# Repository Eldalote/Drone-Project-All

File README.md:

# Drone-Project-All
Project repository for all the components of the Drone project

Project currently on hold. Unfortunately, with the current chip shortage, it would be very difficult to get the PCBs made and populated.
Several important chips are out of stock at all reputable distributors, and I fear that if I try to redesign with parts that I can get, that once I'm done redesigning, some other parts are out of stock.
For now, this project is on hold. I plan to return to it once the chip shortages have been at least somewhat resolved.

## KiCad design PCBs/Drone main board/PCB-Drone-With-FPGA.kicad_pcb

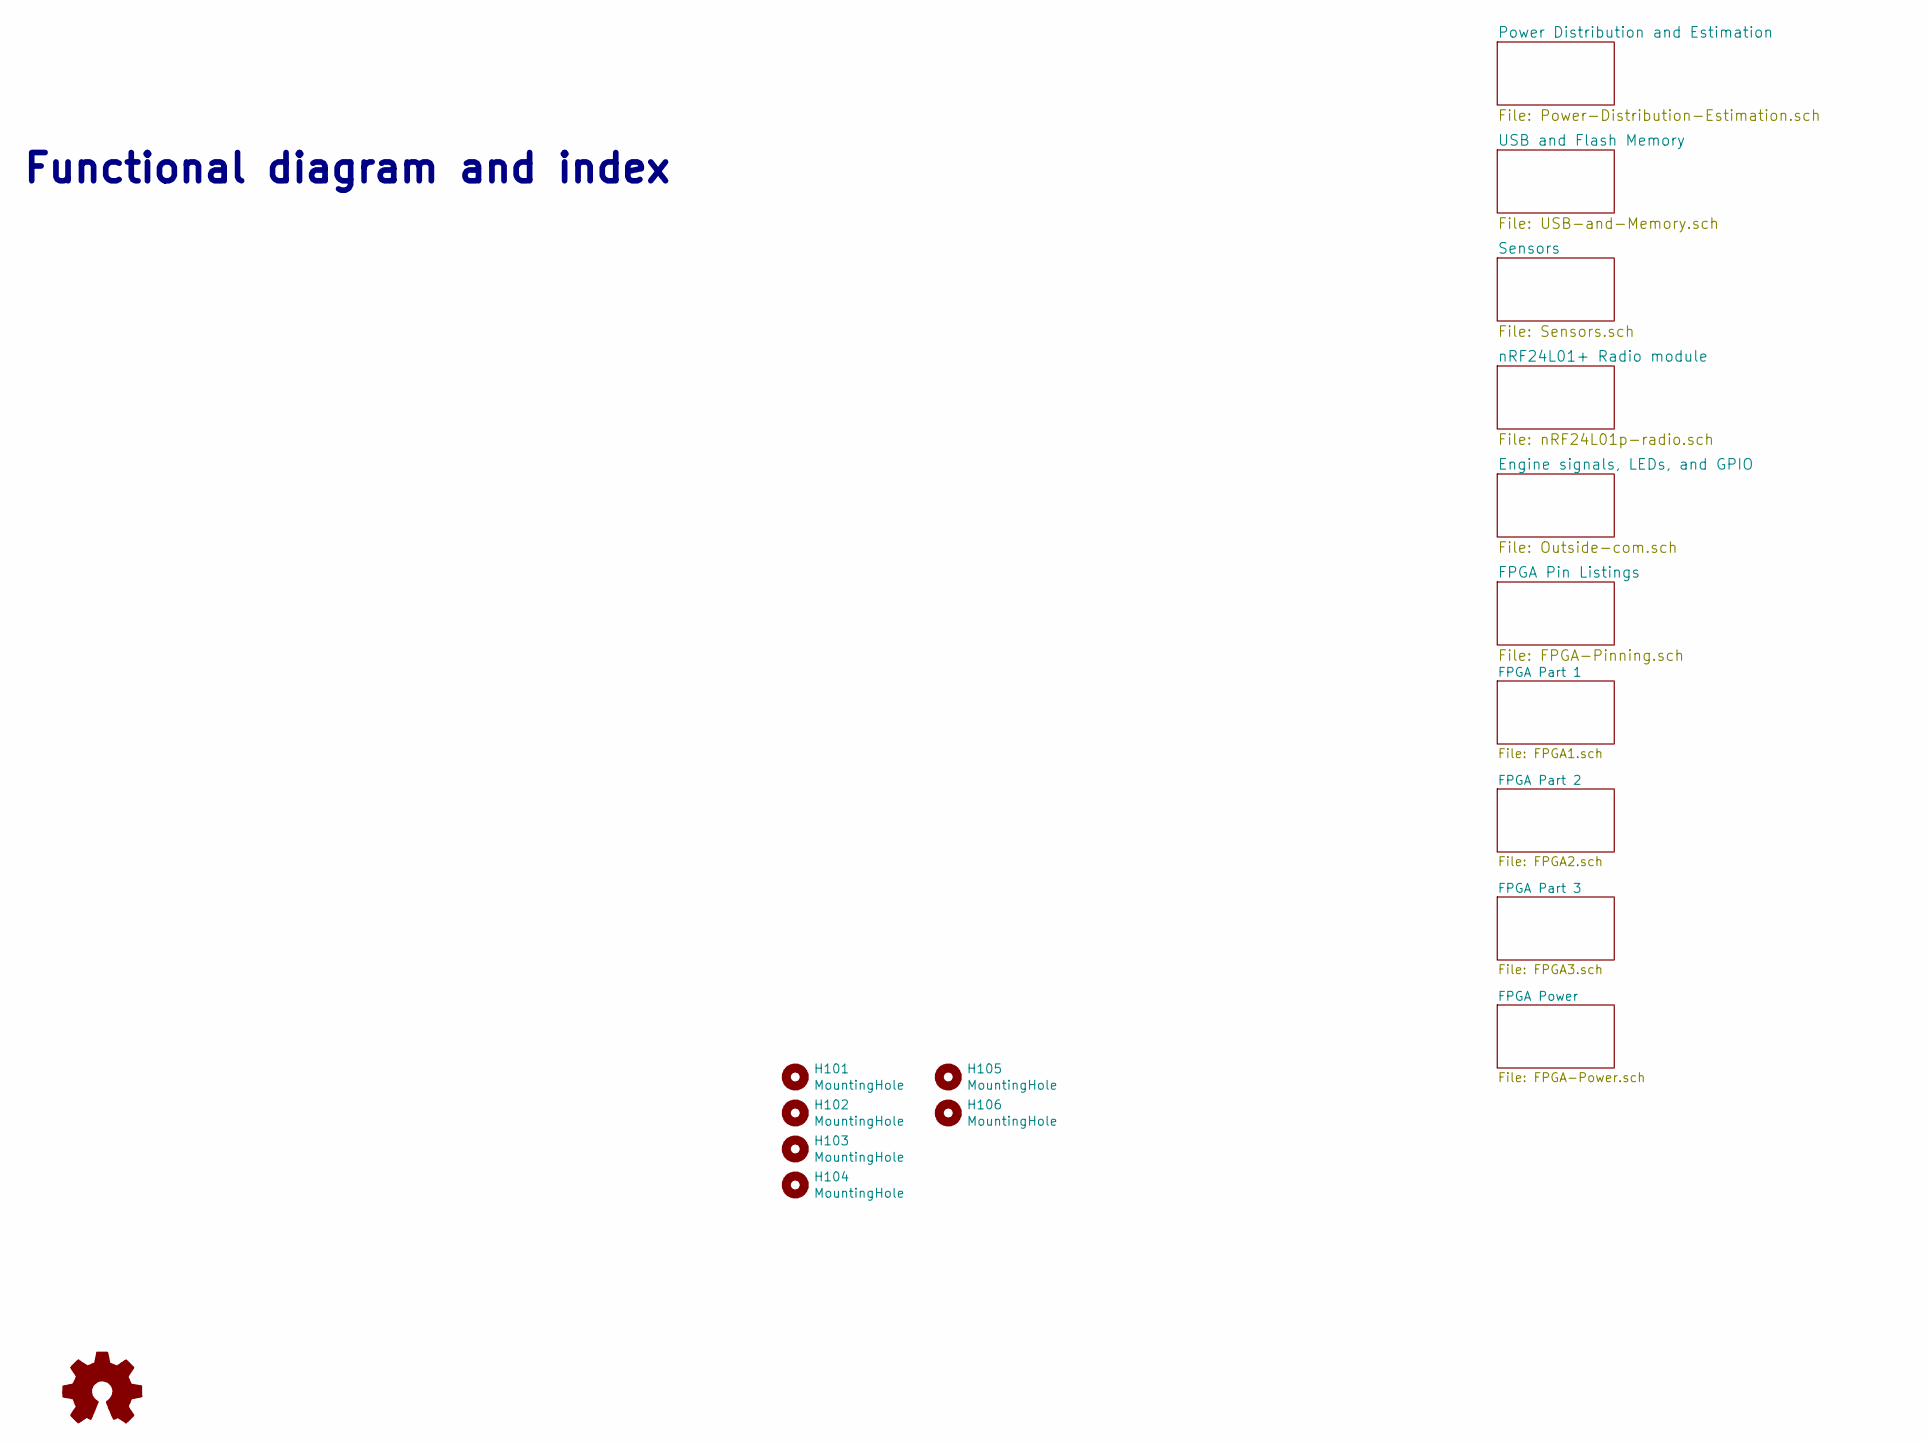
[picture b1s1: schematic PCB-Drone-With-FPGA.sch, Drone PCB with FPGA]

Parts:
H101, H102, H103, H104: MountingHole; MountingHole_3.2mm_M3
H105, H106: MountingHole; MountingHole_6mm
LOGO101: Logo_Open_Hardware_Small; OSHW-Logo_5.7x6mm_SilkScreen

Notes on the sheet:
Functional diagram and index

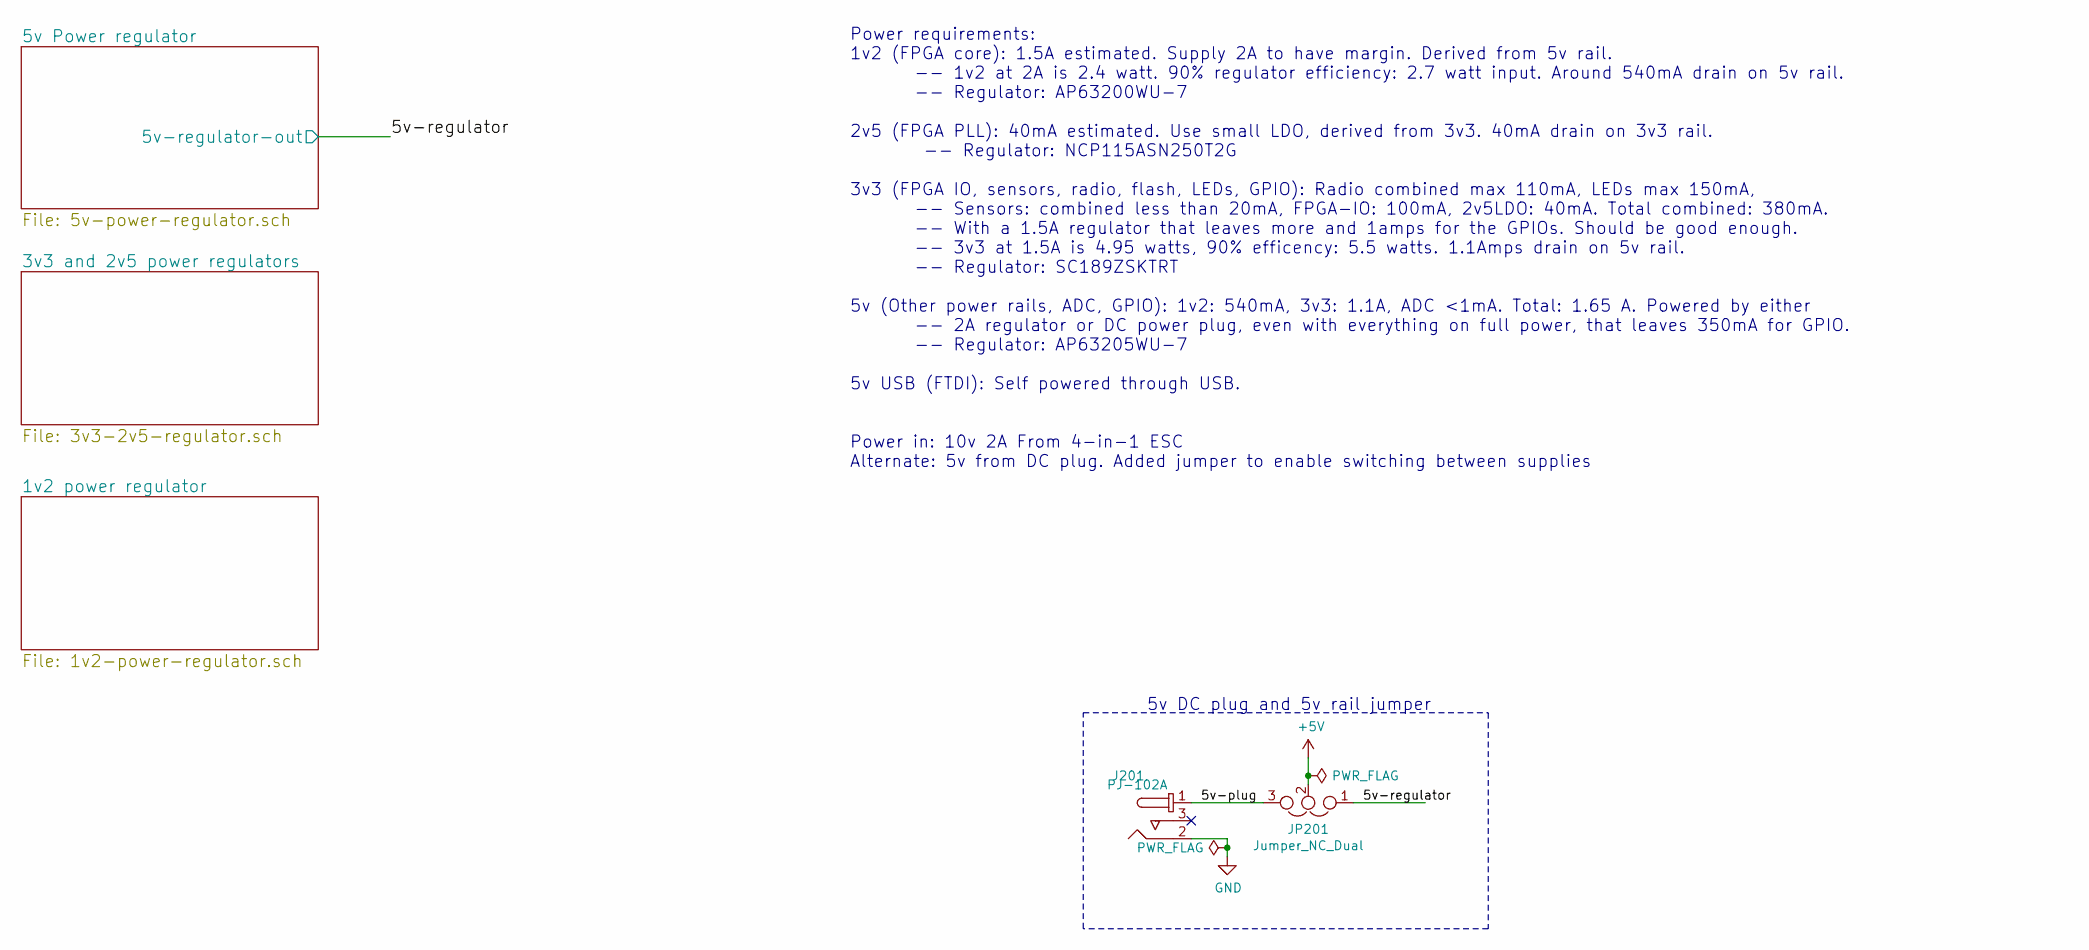
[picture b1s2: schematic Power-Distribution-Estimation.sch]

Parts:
J201: PJ-102A; Barrel_Jack_5.5mmODx2.1mmID_PJ-102A
JP201: Jumper_NC_Dual; PinHeader_1x03_P2.54mm_Vertical

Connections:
+5V: JP201.2; also elsewhere on the board
/Power Distribution and Estimation/5v-plug: J201.1, JP201.3
/Power Distribution and Estimation/5v-regulator: JP201.1; also elsewhere on the board
GND: J201.2; also elsewhere on the board

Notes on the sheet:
Power requirements: 1v2 (FPGA core): 1.5A estimated. Supply 2A to have margin. Derived from 5v rail. -- 1v2 at 2A is 2.4 watt. 90% regulator efficiency: 2.7 watt input. Around 540mA drain on 5v rail. -- Regulator: AP63200WU-7 2v5 (FPGA PLL): 40mA estimated. Use small LDO, derived from 3v3. 40mA dra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
5v DC plug and 5v rail jumper

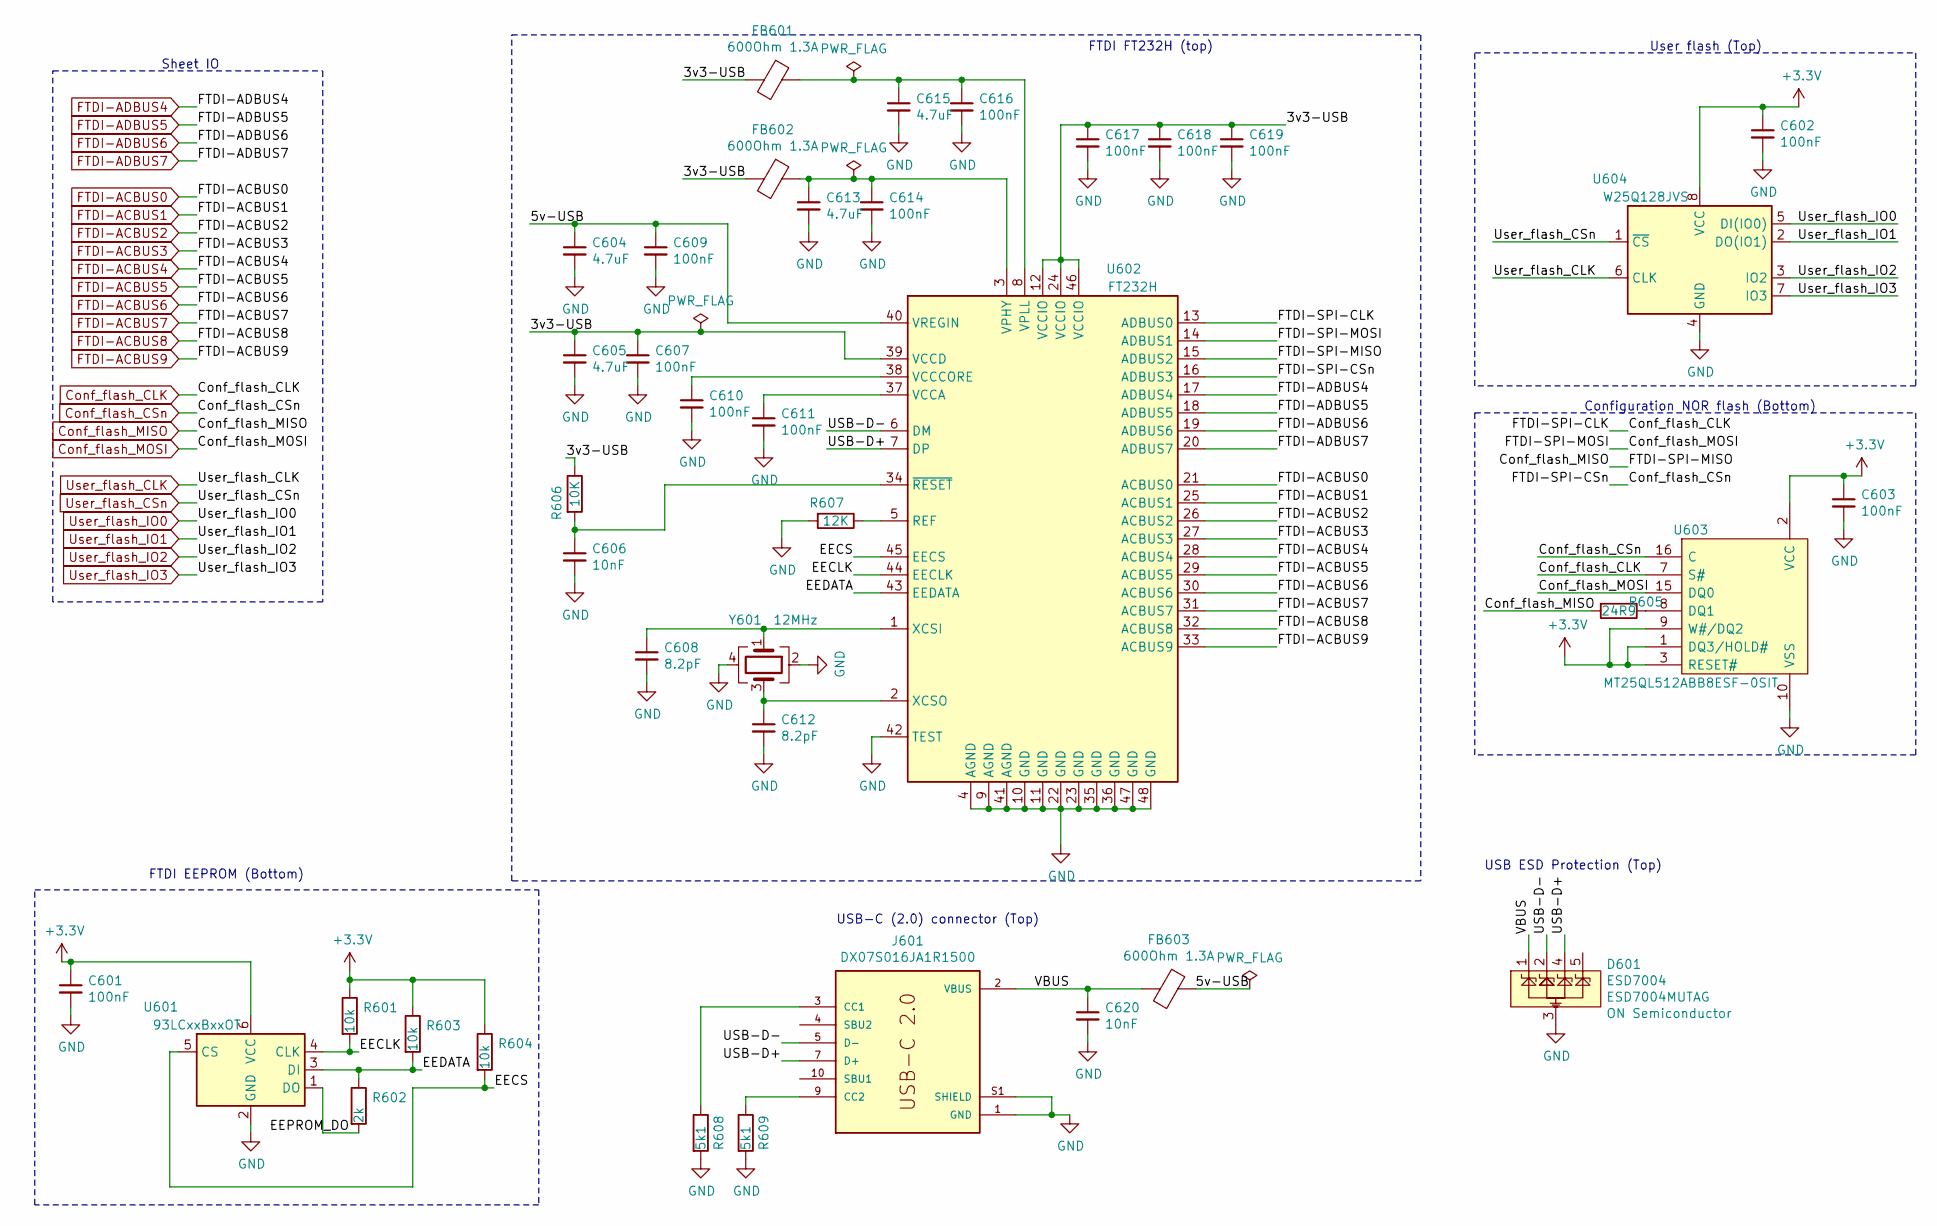
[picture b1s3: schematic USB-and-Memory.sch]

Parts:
C601, C602, C603, C607, C609, C610, C611, C614, C616, C617, C618, C619: 100nF; C_0402_1005Metric
C604, C605, C613, C615: 4.7uF; C_0402_1005Metric
C606, C620: 10nF; C_0402_1005Metric
C608, C612: 8.2pF; C_0402_1005Metric
D601: ESD7004; Diodes_UDFN-10_1.0x2.5mm_P0.5mm
FB601, FB602, FB603: 600Ohm 1.3A; R_0603_1608Metric
J601: DX07S016JA1R1500; JAE_DX07S016JA1R1500
R601, R603, R604: 10k; R_0402_1005Metric
R602: 2k; R_0402_1005Metric
R605: 24R9; R_0402_1005Metric
R606: 10K; R_0402_1005Metric
R607: 12K; R_0402_1005Metric
R608, R609: 5k1; R_0402_1005Metric
U601: 93LCxxBxxOT; SOT-23-6
U602: FT232H; LQFP-48_7x7mm_P0.5mm
U603: MT25QL512ABB8ESF-0SIT; SOIC127P1032X265-16N
U604: W25Q128JVS; SOIC-8_5.23x5.23mm_P1.27mm
Y601: 12MHz; Crystal NDK 3.2x2.5

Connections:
+3V3: C601.1, C602.1, C603.1, R601.1, R603.1, R604.1, U601.6 (VCC), U603.1 (DQ3/HOLD#), U603.2 (VCC), U603.3 (RESET#), U603.9 (W#/DQ2), U604.8 (VCC); also elsewhere on the board
/USB and Flash Memory/3v3-USB: C605.1, C607.1, C617.1, C618.1, C619.1, FB601.2, FB602.2, R606.1, U602.12 (VCCIO), U602.24 (VCCIO), U602.39 (VCCD), U602.46 (VCCIO)
/USB and Flash Memory/5v-USB: C604.1, C609.1, FB603.1, U602.40 (VREGIN)
/USB and Flash Memory/EECLK: R601.2, U601.4 (CLK), U602.44 (EECLK)
/USB and Flash Memory/EECS: R604.2, U601.5 (CS), U602.45 (EECS)
/USB and Flash Memory/EEDATA: R602.1, R603.2, U601.3 (DI), U602.43 (EEDATA)
/USB and Flash Memory/EEPROM_DO: R602.2, U601.1 (DO)
/USB and Flash Memory/USB-D+: D601.4, D601.7 (NC), J601.6 (D+), J601.7 (D+), U602.7 (DP)
/USB and Flash Memory/USB-D-: D601.2, D601.9 (NC), J601.5 (D-), J601.8 (D-), U602.6 (DM)
Conf_flash_CLK: U602.13 (ADBUS0), U603.7 (S#); also elsewhere on the board
Conf_flash_CSn: U602.16 (ADBUS3), U603.16 (C); also elsewhere on the board
Conf_flash_MISO: R605.2, U602.15 (ADBUS2); also elsewhere on the board
Conf_flash_MOSI: U602.14 (ADBUS1), U603.15 (DQ0); also elsewhere on the board
FTDI-ACBUS0: U602.21 (ACBUS0); also elsewhere on the board
FTDI-ACBUS1: U602.25 (ACBUS1); also elsewhere on the board
FTDI-ACBUS2: U602.26 (ACBUS2); also elsewhere on the board
FTDI-ACBUS3: U602.27 (ACBUS3); also elsewhere on the board
FTDI-ACBUS4: U602.28 (ACBUS4); also elsewhere on the board
FTDI-ACBUS5: U602.29 (ACBUS5); also elsewhere on the board
FTDI-ACBUS6: U602.30 (ACBUS6); also elsewhere on the board
FTDI-ACBUS7: U602.31 (ACBUS7); also elsewhere on the board
FTDI-ACBUS8: U602.32 (ACBUS8); also elsewhere on the board
FTDI-ACBUS9: U602.33 (ACBUS9); also elsewhere on the board
FTDI-ADBUS4: U602.17 (ADBUS4); also elsewhere on the board
FTDI-ADBUS5: U602.18 (ADBUS5); also elsewhere on the board
FTDI-ADBUS6: U602.19 (ADBUS6); also elsewhere on the board
FTDI-ADBUS7: U602.20 (ADBUS7); also elsewhere on the board
GND: C601.2, C602.2, C603.2, C604.2, C605.2, C606.2, C607.2, C608.2, C609.2, C610.2, C611.2, C612.2, C613.2, C614.2, C615.2, C616.2, C617.2, C618.2, C619.2, C620.2, D601.3, D601.8 (GND), J601.1 (GND), J601.12 (GND), J601.S1 (SHIELD), J601.S2 (SHIELD), J601.S3 (SHIELD), J601.S4 (SHIELD), J601.S5 (SHIELD), J601.S6 (SHIELD), R607.2, R608.2, R609.2, U601.2 (GND), U602.4 (AGND), U602.9 (AGND), U602.10 (GND), U602.11 (GND), U602.22 (GND), U602.23 (GND), U602.35 (GND), U602.36 (GND), U602.41 (AGND), U602.42 (TEST), U602.47 (GND), U602.48 (GND), U603.10 (VSS), U604.4 (GND), Y601.2, Y601.4; also elsewhere on the board
unnamed: C606.1, R606.2, U602.34 (~RESET)
unnamed: C608.1, U602.1 (XCSI), Y601.1
unnamed: C610.1, U602.38 (VCCCORE)
unnamed: C611.1, U602.37 (VCCA)
unnamed: C612.1, U602.2 (XCSO), Y601.3
unnamed: C613.1, C614.1, FB602.1, U602.3 (VPHY)
unnamed: C615.1, C616.1, FB601.1, U602.8 (VPLL)
unnamed: D601.5, D601.6 (NC)
unnamed: J601.3 (CC1), R608.1
unnamed: J601.9 (CC2), R609.1
unnamed: R605.1, U603.8 (DQ1)
unnamed: R607.1, U602.5 (REF)
User_flash_CLK: U604.6 (CLK); also elsewhere on the board
User_flash_CSn: U604.1 (~CS); also elsewhere on the board
User_flash_IO0: U604.5 (DI(IO0)); also elsewhere on the board
User_flash_IO1: U604.2 (DO(IO1)); also elsewhere on the board
User_flash_IO2: U604.3 (IO2); also elsewhere on the board
User_flash_IO3: U604.7 (IO3); also elsewhere on the board
VBUS: C620.1, D601.1, D601.10 (NC), FB603.2, J601.2 (VBUS), J601.11 (VBUS)

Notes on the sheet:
Configuration NOR flash (Bottom)
User flash (Top)
FTDI EEPROM (Bottom)
FTDI FT232H (top)
USB-C (2.0) connector (Top)
Sheet IO
USB ESD Protection (Top)

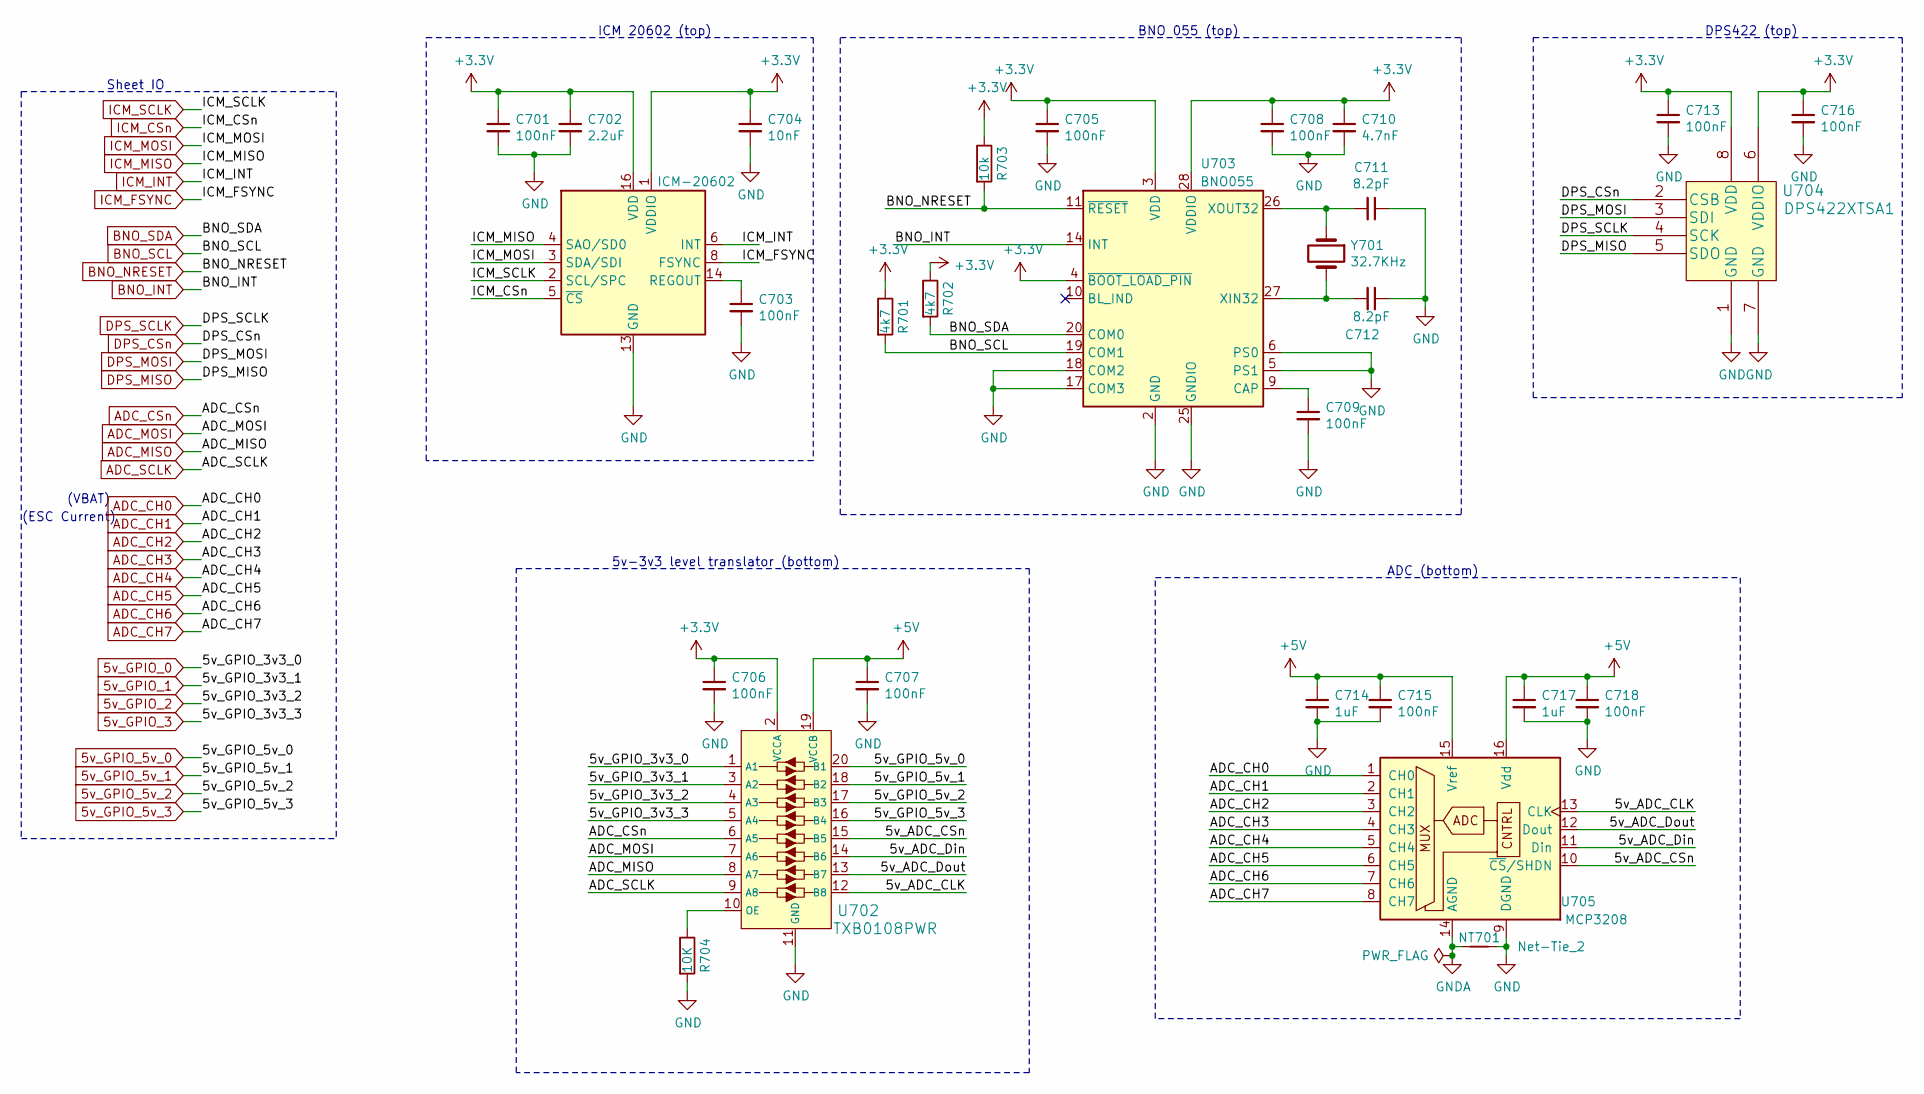
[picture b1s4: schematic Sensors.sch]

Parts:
C701, C703, C705, C706, C707, C708, C709, C713, C715, C716, C718: 100nF; C_0402_1005Metric
C702: 2.2uF; C_0603_1608Metric
C704: 10nF; C_0402_1005Metric
C710: 4.7nF; C_0402_1005Metric
C711, C712: 8.2pF; C_0402_1005Metric
C714, C717: 1uF; C_0603_1608Metric
NT701: Net-Tie_2; NetTie-2_SMD_Pad0.5mm
R701, R702: 4k7; R_0402_1005Metric
R703: 10k; R_0402_1005Metric
R704: 10K; R_0402_1005Metric
U701: ICM-20602; LGA-16_3x3mm_P0.5mm_LayoutBorder3x5y
U702: TXB0108PWR; TSSOP-20_W4.4mm
U703: BNO055; LGA-28_5.2x3.8mm_P0.5mm
U704: DPS422XTSA1
U705: MCP3208; SOIC-16_3.9x9.9mm_P1.27mm
Y701: 32.7KHz; Crystal_SMD_3215-2Pin_3.2x1.5mm

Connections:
5v_GPIO_0: U702.1 (A1); also elsewhere on the board
5v_GPIO_1: U702.3 (A2); also elsewhere on the board
5v_GPIO_2: U702.4 (A3); also elsewhere on the board
5v_GPIO_3: U702.5 (A4); also elsewhere on the board
5v_GPIO_5v_0: U702.20 (B1); also elsewhere on the board
5v_GPIO_5v_1: U702.18 (B2); also elsewhere on the board
5v_GPIO_5v_2: U702.17 (B3); also elsewhere on the board
5v_GPIO_5v_3: U702.16 (B4); also elsewhere on the board
+3V3: C701.1, C702.1, C704.1, C705.1, C706.1, C708.1, C710.1, C713.1, C716.1, R701.1, R702.1, R703.1, U701.1 (VDDIO), U701.16 (VDD), U702.2 (VCCA), U703.3 (VDD), U703.4 (~BOOT_LOAD_PIN), U703.28 (VDDIO), U704.6 (VDDIO), U704.8 (VDD); also elsewhere on the board
+5V: C707.1, C714.1, C715.1, C717.1, C718.1, U702.19 (VCCB), U705.15 (Vref), U705.16 (Vdd); also elsewhere on the board
/Sensors/5v_ADC_CLK: U702.12 (B8), U705.13 (CLK)
/Sensors/5v_ADC_CSn: U702.15 (B5), U705.10 (~CS~/SHDN)
/Sensors/5v_ADC_Din: U702.14 (B6), U705.11 (Din)
/Sensors/5v_ADC_Dout: U702.13 (B7), U705.12 (Dout)
ADC_CH0: U705.1 (CH0); also elsewhere on the board
ADC_CH1: U705.2 (CH1); also elsewhere on the board
ADC_CH2: U705.3 (CH2); also elsewhere on the board
ADC_CH3: U705.4 (CH3); also elsewhere on the board
ADC_CH4: U705.5 (CH4); also elsewhere on the board
ADC_CH5: U705.6 (CH5); also elsewhere on the board
ADC_CH6: U705.7 (CH6); also elsewhere on the board
ADC_CH7: U705.8 (CH7); also elsewhere on the board
ADC_CSn: U702.6 (A5); also elsewhere on the board
ADC_MISO: U702.8 (A7); also elsewhere on the board
ADC_MOSI: U702.7 (A6); also elsewhere on the board
ADC_SCLK: U702.9 (A8); also elsewhere on the board
BNO_INT: U703.14 (INT); also elsewhere on the board
BNO_NRESET: R703.2, U703.11 (~RESET); also elsewhere on the board
BNO_SCL: R701.2, U703.19 (COM1); also elsewhere on the board
BNO_SDA: R702.2, U703.20 (COM0); also elsewhere on the board
DPS_CSn: U704.2 (CSB); also elsewhere on the board
DPS_MISO: U704.5 (SDO); also elsewhere on the board
DPS_MOSI: U704.3 (SDI); also elsewhere on the board
DPS_SCLK: U704.4 (SCK); also elsewhere on the board
GND: C701.2, C702.2, C703.2, C704.2, C705.2, C706.2, C707.2, C708.2, C709.2, C710.2, C711.1, C712.1, C713.2, C714.2, C715.2, C716.2, C717.2, C718.2, NT701.2, R704.2, U701.9 (GND), U701.10 (GND), U701.11 (GND), U701.12 (GND), U701.13 (GND), U701.15 (GND), U702.11 (GND), U703.2 (GND), U703.5 (PS1), U703.6 (PS0), U703.15 (GNDIO), U703.16 (GNDIO), U703.17 (COM3), U703.18 (COM2), U703.25 (GNDIO), U704.1 (GND), U704.7 (GND), U705.9 (DGND); also elsewhere on the board
GNDA: NT701.1, U705.14 (AGND); also elsewhere on the board
ICM_CSn: U701.5 (~CS); also elsewhere on the board
ICM_FSYNC: U701.8 (FSYNC); also elsewhere on the board
ICM_INT: U701.6 (INT); also elsewhere on the board
ICM_MISO: U701.4 (SAO/SD0); also elsewhere on the board
ICM_MOSI: U701.3 (SDA/SDI); also elsewhere on the board
ICM_SCLK: U701.2 (SCL/SPC); also elsewhere on the board
unnamed: C703.1, U701.14 (REGOUT)
unnamed: C709.1, U703.9 (CAP)
unnamed: C711.2, U703.26 (XOUT32), Y701.1
unnamed: C712.2, U703.27 (XIN32), Y701.2
unnamed: R704.1, U702.10 (OE)

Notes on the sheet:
ICM 20602 (top)
BNO 055 (top)
DPS422 (top)
Sheet IO
5v-3v3 level translator (bottom)
ADC (bottom)
(VBAT)
(ESC Current)

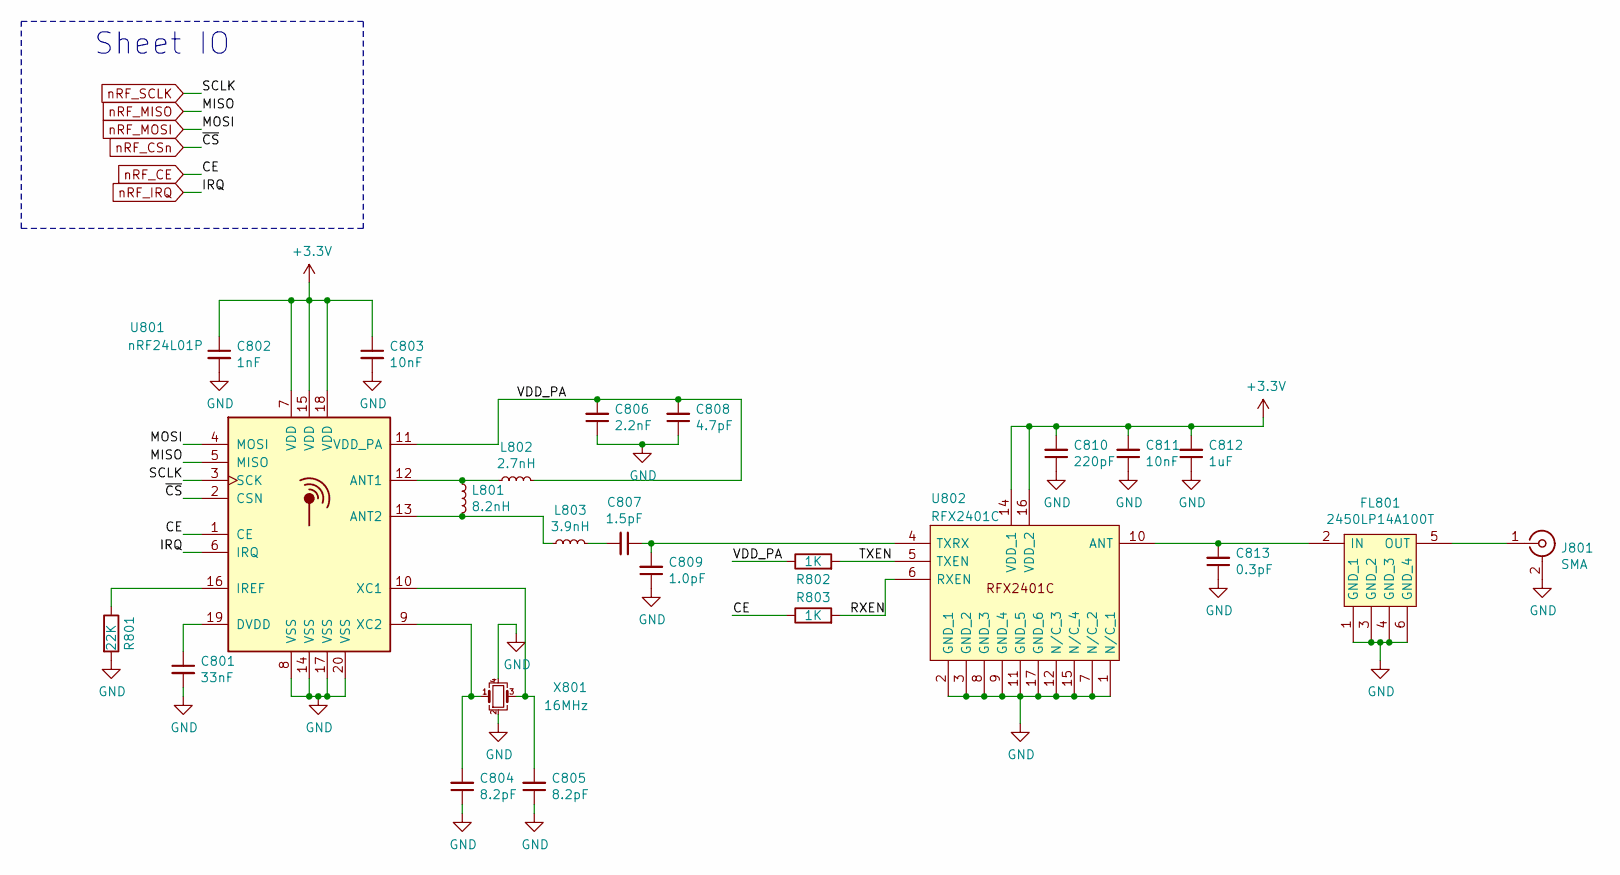
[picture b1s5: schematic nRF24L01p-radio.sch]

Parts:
C801: 33nF; C_0603_1608Metric
C802: 1nF; C_0402_1005Metric
C803, C811: 10nF; C_0402_1005Metric
C804, C805: 8.2pF; C_0402_1005Metric
C806: 2.2nF; C_0402_1005Metric
C807: 1.5pF; C_0402_1005Metric
C808: 4.7pF; C_0402_1005Metric
C809: 1.0pF; C_0603_1608Metric_Pad1.05x0.95mm_HandSolder
C810: 220pF; C_0402_1005Metric
C812: 1uF; C_0603_1608Metric
C813: 0.3pF; C_0402_1005Metric
FL801: 2450LP14A100T
J801: SMA; SMA_Samtec_SMA-J-P-X-ST-EM1_EdgeMount
L801: 8.2nH; L_0402_1005Metric
L802: 2.7nH; L_0402_1005Metric
L803: 3.9nH; L_0402_1005Metric
R801: 22K; R_0402_1005Metric
R802, R803: 1K; R_0402_1005Metric
U801: nRF24L01P; nRF24L01P-QFN-20-1EP_4x4mm_P0.5mm_EP
U802: RFX2401C; QFN-16-1EP_3x3mm_P0.5mm_EP1.75x1.75mm
X801: 16MHz; Crystal NDK 3.2x2.5

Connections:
+3V3: C802.1, C803.1, C810.2, C811.2, C812.2, U801.7 (VDD), U801.15 (VDD), U801.18 (VDD), U802.14 (VDD_1), U802.16 (VDD_2); also elsewhere on the board
/nRF24L01+ Radio module/RXEN: R803.2, U802.6 (RXEN)
/nRF24L01+ Radio module/TXEN: R802.2, U802.5 (TXEN)
/nRF24L01+ Radio module/VDD_PA: C806.2, C808.2, L802.2, R802.1, U801.11 (VDD_PA)
GND: C801.2, C802.2, C803.2, C804.1, C805.1, C806.1, C808.1, C809.1, C810.1, C811.1, C812.1, C813.1, FL801.1 (GND_1), FL801.3 (GND_2), FL801.4 (GND_3), FL801.6 (GND_4), J801.2 (Ext), R801.2, U801.8 (VSS), U801.14 (VSS), U801.17 (VSS), U801.20 (VSS), U801.21 (EP), U802.1 (N/C_1), U802.2 (GND_1), U802.3 (GND_2), U802.7 (N/C_2), U802.8 (GND_3), U802.9 (GND_4), U802.11 (GND_5), U802.12 (N/C_3), U802.15 (N/C_4), U802.17 (GND_6), X801.2, X801.4; also elsewhere on the board
unnamed: C801.1, U801.19 (DVDD)
unnamed: C804.2, U801.9 (XC2), X801.1
unnamed: C805.2, U801.10 (XC1), X801.3
unnamed: C807.1, C809.2, U802.4 (TXRX)
unnamed: C807.2, L803.2
unnamed: C813.2, FL801.2 (IN), U802.10 (ANT)
unnamed: FL801.5 (OUT), J801.1 (In)
unnamed: L801.1, L802.1, U801.12 (ANT1)
unnamed: L801.2, L803.1, U801.13 (ANT2)
unnamed: R801.1, U801.16 (IREF)
nRF_CE: R803.1, U801.1 (CE); also elsewhere on the board
nRF_CSn: U801.2 (CSN); also elsewhere on the board
nRF_IRQ: U801.6 (IRQ); also elsewhere on the board
nRF_MISO: U801.5 (MISO); also elsewhere on the board
nRF_MOSI: U801.4 (MOSI); also elsewhere on the board
nRF_SCLK: U801.3 (SCK); also elsewhere on the board

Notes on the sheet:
Sheet IO

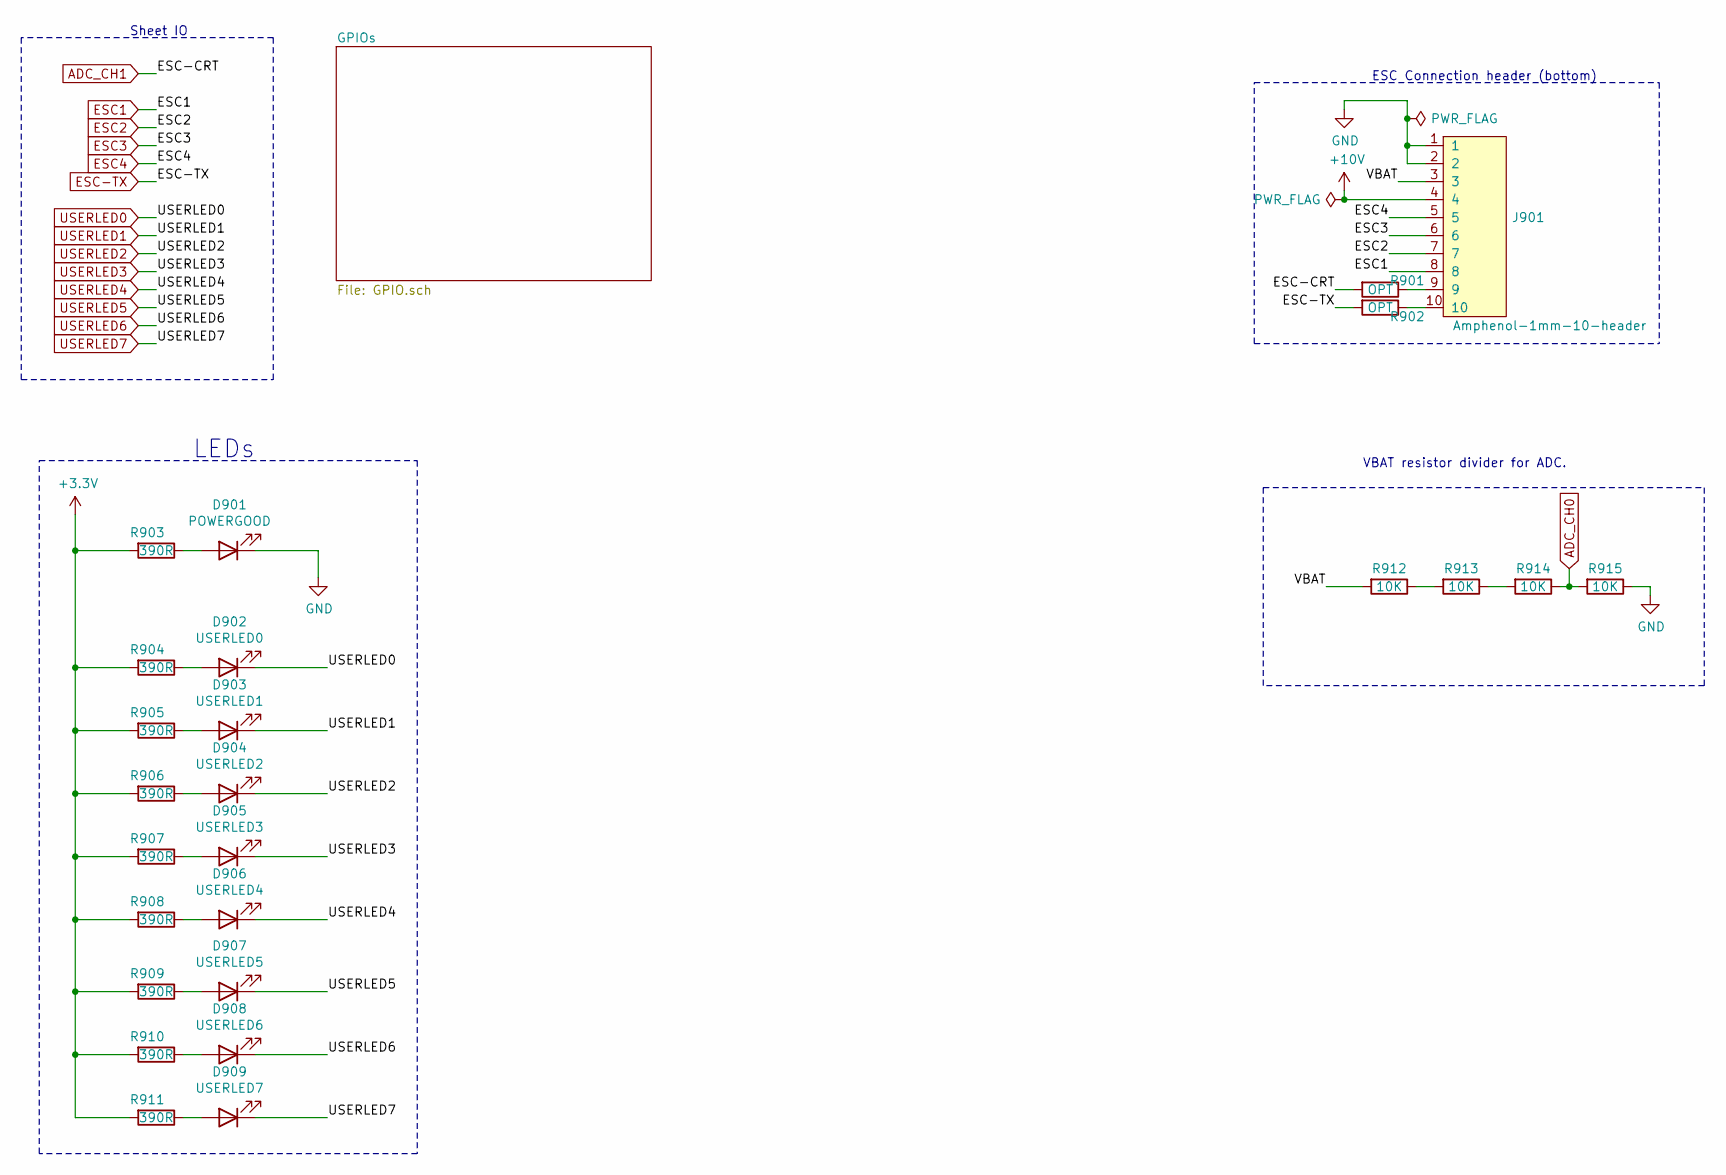
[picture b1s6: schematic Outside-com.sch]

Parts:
D901: POWERGOOD; LED_0603_1608Metric
D902: USERLED0; LED_0603_1608Metric
D903: USERLED1; LED_0603_1608Metric
D904: USERLED2; LED_0603_1608Metric
D905: USERLED3; LED_0603_1608Metric
D906: USERLED4; LED_0603_1608Metric
D907: USERLED5; LED_0603_1608Metric
D908: USERLED6; LED_0603_1608Metric
D909: USERLED7; LED_0603_1608Metric
J901: Amphenol-1mm-10-header; Amphenol-10-1mm
R901, R902: OPT; R_0402_1005Metric
R903, R904, R905, R906, R907, R908, R909, R910, R911: 390R; R_0402_1005Metric
R912, R913, R914, R915: 10K; R_0402_1005Metric

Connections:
+3V3: R903.2, R904.2, R905.2, R906.2, R907.2, R908.2, R909.2, R910.2, R911.2; also elsewhere on the board
+10V: J901.4; also elsewhere on the board
/Engine signals, LEDs, and GPIO/VBAT: J901.3, R912.2
ADC_CH0: R914.1, R915.2; also elsewhere on the board
ADC_CH1: R901.2; also elsewhere on the board
ESC1: J901.8; also elsewhere on the board
ESC2: J901.7; also elsewhere on the board
ESC3: J901.6; also elsewhere on the board
ESC4: J901.5; also elsewhere on the board
ESC-TX: R902.2; also elsewhere on the board
GND: D901.1 (K), J901.1, J901.2, R915.1; also elsewhere on the board
unnamed: D901.2 (A), R903.1
unnamed: D902.2 (A), R904.1
unnamed: D903.2 (A), R905.1
unnamed: D904.2 (A), R906.1
unnamed: D905.2 (A), R907.1
unnamed: D906.2 (A), R908.1
unnamed: D907.2 (A), R909.1
unnamed: D908.2 (A), R910.1
unnamed: D909.2 (A), R911.1
unnamed: J901.9, R901.1
unnamed: J901.10, R902.1
unnamed: R912.1, R913.2
unnamed: R913.1, R914.2
USERLED0: D902.1 (K); also elsewhere on the board
USERLED1: D903.1 (K); also elsewhere on the board
USERLED2: D904.1 (K); also elsewhere on the board
USERLED3: D905.1 (K); also elsewhere on the board
USERLED4: D906.1 (K); also elsewhere on the board
USERLED5: D907.1 (K); also elsewhere on the board
USERLED6: D908.1 (K); also elsewhere on the board
USERLED7: D909.1 (K); also elsewhere on the board

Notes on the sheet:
ESC Connection header (bottom)
Sheet IO
LEDs
VBAT resistor divider for ADC.
